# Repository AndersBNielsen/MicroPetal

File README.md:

# MicroPetal Uno R1

[Get the MicroPetal Uno R1 Founders Edition at iMania](https://www.imania.dk/micropetal-uno-r1-founders-edition.htm).

Arduino Uno-format board accommodating PY32F071 and PY32F072. The initial assembly and software target is **PY32F071C1BU6**; F072 software support is not implemented yet.

## Hardware

KiCad sources and fabrication outputs are at the repository root and in `production/`.

## Software

The experimental Arduino core, PlatformIO platform, tools and examples live in [`software/`](software/README.md).

- [Arduino beginner guide](software/docs/ARDUINO-START.md)
- [PlatformIO beginner guide](software/docs/PLATFORMIO-START.md)
- [Schematic analysis and first-power instructions](software/docs/SCHEMATIC-ANALYSIS.md)

Software is compile-tested, not yet hardware-validated.

Run software commands from `software/`, e.g. `cd software` before following either guide.

## Getting a PCB

Prefer a ready-made board? [Get the MicroPetal Uno R1 Founders Edition at iMania](https://www.imania.dk/micropetal-uno-r1-founders-edition.htm). To manufacture your own, use the files in [`production/`](production/).
This project is kindly sponsored by JLCPCB. They offer cheap, professional looking PCBs and super fast delivery.

Step 1: Get the gerber file zip package from the /hardware folder
/hardware/rev2/rev2-1316.zip for instance.

Step 2: Upload to JLCPCB [https://jlcpcb.com](https://jlcpcb.com/?from=Anders_N)

Step 3: Pick your color, surface finish and order.

If you want JLCPCB to assemble a board, the BOM and placement files are also in the repo. 

You can use these affiliate links to get a board for $2 and also get $80 worth of New User Coupons at: https://jlcpcb.com/?from=Anders_N

And in case you also want to order a 3D-printed case you can use this link. 
How to Get a $7 3D Printing Coupon: https://jlc3dp.com/?from=Anders_N

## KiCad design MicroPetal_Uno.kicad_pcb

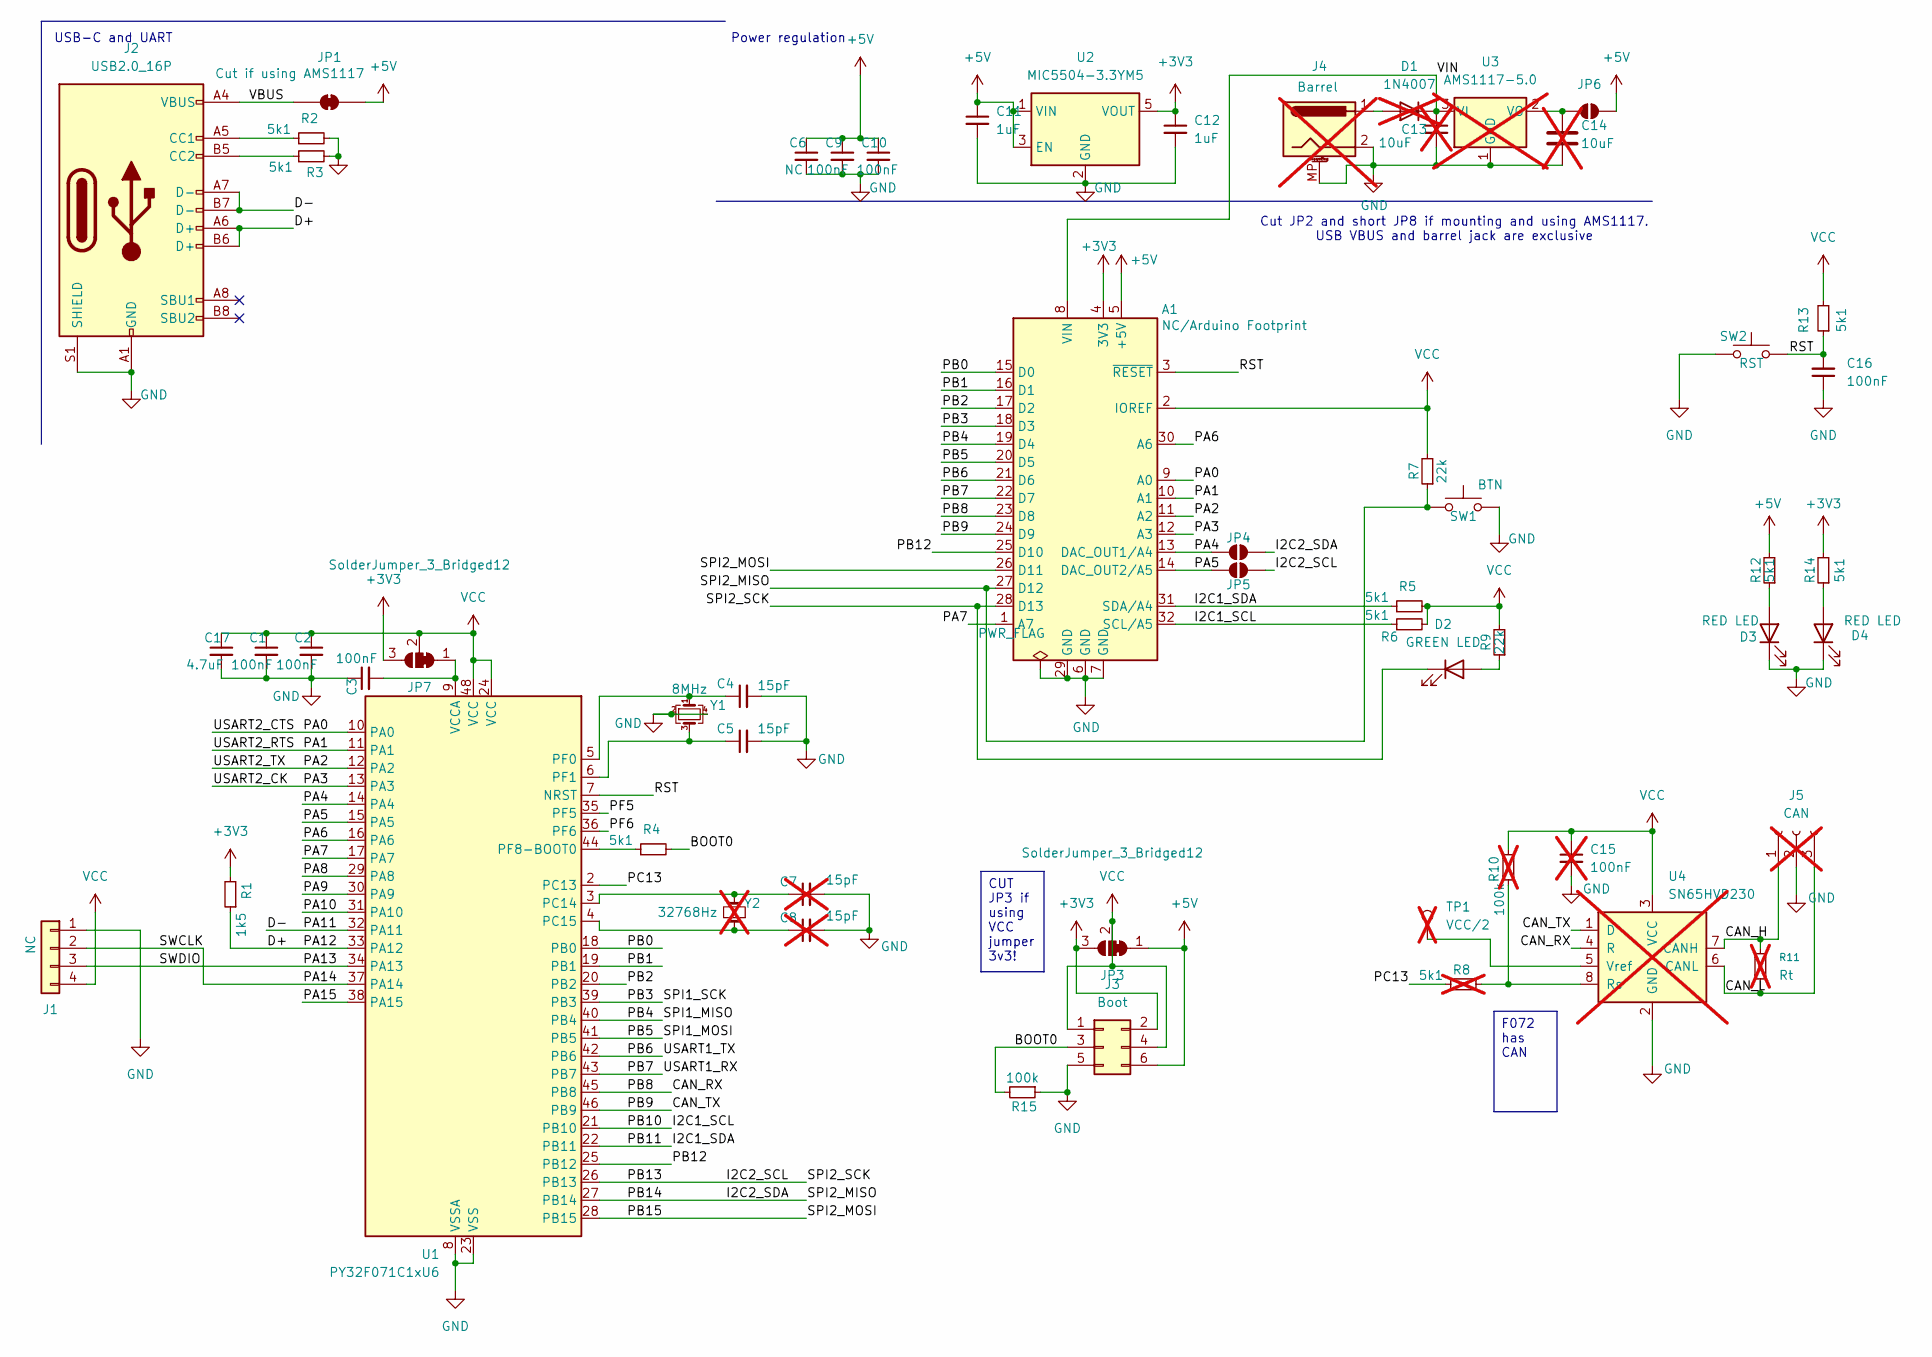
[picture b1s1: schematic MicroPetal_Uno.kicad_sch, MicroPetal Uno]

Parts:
A1: NC/Arduino Footprint; Arduino_UNO_R3_WithMountingHoles
C1, C2, C3, C9, C10, C16: 100nF; C_0402_1005Metric; LCSC C49678
C4, C5: 15pF; C_0402_1005Metric; LCSC C1548
C6: NC; C_0805_2012Metric
C7, C8: 15pF; C_0402_1005Metric; LCSC C1548; not fitted
C11, C12: 1uF; C_0805_2012Metric; LCSC C28323
C13, C14: 10uF; C_1206_3216Metric; LCSC C13585; not fitted
C15: 100nF; C_0402_1005Metric; LCSC C307331; not fitted
C17: 4.7uF; C_0603_1608Metric; LCSC C19666
D1: 1N4007; D_SMA; LCSC C95872; not fitted
D2: GREEN LED; LED_0805_2012Metric; LCSC C2297
D3, D4: RED LED; LED_0805_2012Metric; LCSC C84256
J1: NC; PinHeader_1x04_P2.54mm_Vertical
J2: USB2.0_16P; USB_C_Receptacle_HCTL_HC-TYPE-C-16P-01A; LCSC C2894897
J3: Boot; PinHeader_2x03_P2.54mm_Vertical
J4: Barrel; BarrelJack_Horizontal; not fitted
J5: CAN; PinHeader_1x03_P2.54mm_Vertical; not fitted
JP1: Cut if using AMS1117; SolderJumper-2_P1.3mm_Bridged_RoundedPad1.0x1.5mm
JP3, JP7: SolderJumper_3_Bridged12; SolderJumper-3_P1.3mm_Bridged12_RoundedPad1.0x1.5mm
JP4, JP5, JP6: SolderJumper_2_Open; SolderJumper-2_P1.3mm_Open_RoundedPad1.0x1.5mm
R1: 1k5; R_0402_1005Metric; LCSC C25867
R2, R3, R4, R5, R6, R12, R13, R14: 5k1; R_0402_1005Metric; LCSC C25905
R7, R9: 22k; R_0805_2012Metric; LCSC C17560
R8: 5k1; R_0402_1005Metric; LCSC C25905; not fitted
R10: 100k; R_0402_1005Metric; LCSC C25905; not fitted
R11: Rt; R_0805_2012Metric; not fitted
R15: 100k; R_0402_1005Metric; LCSC C25741
SW1: BTN; SW_SPST_TL3342; LCSC C318884
SW2: RST; SW_SPST_TL3342; LCSC C318884
TP1: VCC/2; TestPoint_Pad_D1.0mm; not fitted
U1: PY32F071C1xU6; QFN-48-1EP_6x6mm_P0.4mm_EP4.4x4.4mm; LCSC C7434410
U2: MIC5504-3.3YM5; SOT-23-5; LCSC C3021093
U3: AMS1117-5.0; SOT-223-3_TabPin2; LCSC C347223; not fitted
U4: SN65HVD230; SOIC-8_3.9x4.9mm_P1.27mm; LCSC C12084; not fitted
Y1: 8MHz; Crystal_SMD_3225-4Pin_3.2x2.5mm; LCSC C5308002
Y2: 32768Hz; Crystal_SMD_3215-2Pin_3.2x1.5mm; LCSC C32346; not fitted

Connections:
+3V3: A1.4 (3V3), C12.1, J3.2, JP3.3 (B), JP7.3 (B), R1.2, R14.2, U2.5 (VOUT)
+5V: A1.5 (+5V), C6.1, C9.1, C10.1, C11.1, J3.6, JP1.2 (B), JP3.1 (A), JP6.2 (B), R12.2, U2.1 (VIN), U2.3 (EN)
/BOOT0: J3.3, R4.2, R15.2
/CAN_H: J5.1, R11.1, U4.7 (CANH)
/CAN_L: J5.3, R11.2, U4.6 (CANL)
/CAN_RX: A1.23 (D8), U1.45 (PB8), U4.4 (R)
/CAN_TX: A1.24 (D9), U1.46 (PB9), U4.1 (D)
/D+: J2.A6 (D+), J2.B6 (D+), R1.1, U1.33 (PA12)
/D-: J2.A7 (D-), J2.B7 (D-), U1.32 (PA11)
/I2C1_SCL: A1.32 (SCL/A5), R6.1, U1.21 (PB10)
/I2C1_SDA: A1.31 (SDA/A4), R5.1, U1.22 (PB11)
/I2C2_SCL: A1.28 (D13), D2.1 (K), JP5.2 (B), U1.26 (PB13)
/I2C2_SDA: A1.27 (D12), JP4.2 (B), R7.1, SW1.1, U1.27 (PB14)
/PA0: A1.9 (A0), U1.10 (PA0)
/PA1: A1.10 (A1), U1.11 (PA1)
/PA2: A1.11 (A2), U1.12 (PA2)
/PA3: A1.12 (A3), U1.13 (PA3)
/PA4: A1.13 (DAC_OUT1/A4), JP4.1 (A), U1.14 (PA4)
/PA5: A1.14 (DAC_OUT2/A5), JP5.1 (A), U1.15 (PA5)
/PA6: A1.30 (A6), U1.16 (PA6)
/PA7: A1.1 (A7), U1.17 (PA7)
/PA8: U1.29 (PA8)
/PA9: U1.30 (PA9)
/PA10: U1.31 (PA10)
/PA13: J1.3, U1.34 (PA13)
/PA14: J1.2, U1.37 (PA14)
/PA15: U1.38 (PA15)
/PB0: A1.15 (D0), U1.18 (PB0)
/PB1: A1.16 (D1), U1.19 (PB1)
/PB2: A1.17 (D2), U1.20 (PB2)
/PB3: A1.18 (D3), U1.39 (PB3)
/PB4: A1.19 (D4), U1.40 (PB4)
/PB5: A1.20 (D5), U1.41 (PB5)
/PB6: A1.21 (D6), U1.42 (PB6)
/PB7: A1.22 (D7), U1.43 (PB7)
/PB12: A1.25 (D10), U1.25 (PB12)
/PB15: A1.26 (D11), U1.28 (PB15)
/PC13: R8.1, U1.2 (PC13)
/PF6: U1.36 (PF6)
/RST: A1.3 (~RESET), C16.2, R13.1, SW2.2, U1.7 (NRST)
/VBUS: J2.A4 (VBUS), J2.A9 (VBUS), J2.B4 (VBUS), J2.B9 (VBUS), JP1.1 (A)
/VIN: A1.8 (VIN), C13.1, D1.1 (K), U3.3 (VI)
unnamed: D1.2 (A), J4.1
unnamed: D2.2 (A), R9.1
unnamed: D3.2 (A), R12.1
unnamed: D4.2 (A), R14.1
unnamed: J2.A5 (CC1), R2.1
unnamed: J2.B5 (CC2), R3.1
unnamed: C14.1, JP6.1 (A), U3.2 (VO)
unnamed: C3.2, JP7.1 (A), U1.9 (VCCA)
unnamed: C7.1, U1.3 (PC14), Y2.2
unnamed: C8.1, U1.4 (PC15), Y2.1
unnamed: C4.1, U1.5 (PF0), Y1.1
unnamed: C5.1, U1.6 (PF1), Y1.3
unnamed: R4.1, U1.44 (PF8-BOOT0)
unnamed: R8.2, R10.1, U4.8 (Rs)
unnamed: TP1.1 (1_1), U4.5 (Vref)
VCC: A1.2 (IOREF), C1.1, C2.1, C15.1, C17.1, J1.4, J3.1, J3.4, JP3.2 (C), JP7.2 (C), R5.2, R6.2, R7.2, R9.2, R10.2, R13.2, U1.24 (VCC), U1.48 (VCC), U4.3 (VCC)

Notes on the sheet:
Cut JP2 and short JP8 if mounting and using AMS1117. USB VBUS and barrel jack are exclusive
Power regulation
USB-C and UART
F072 has CAN
CUT JP3 if using VCC jumper 3v3!

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
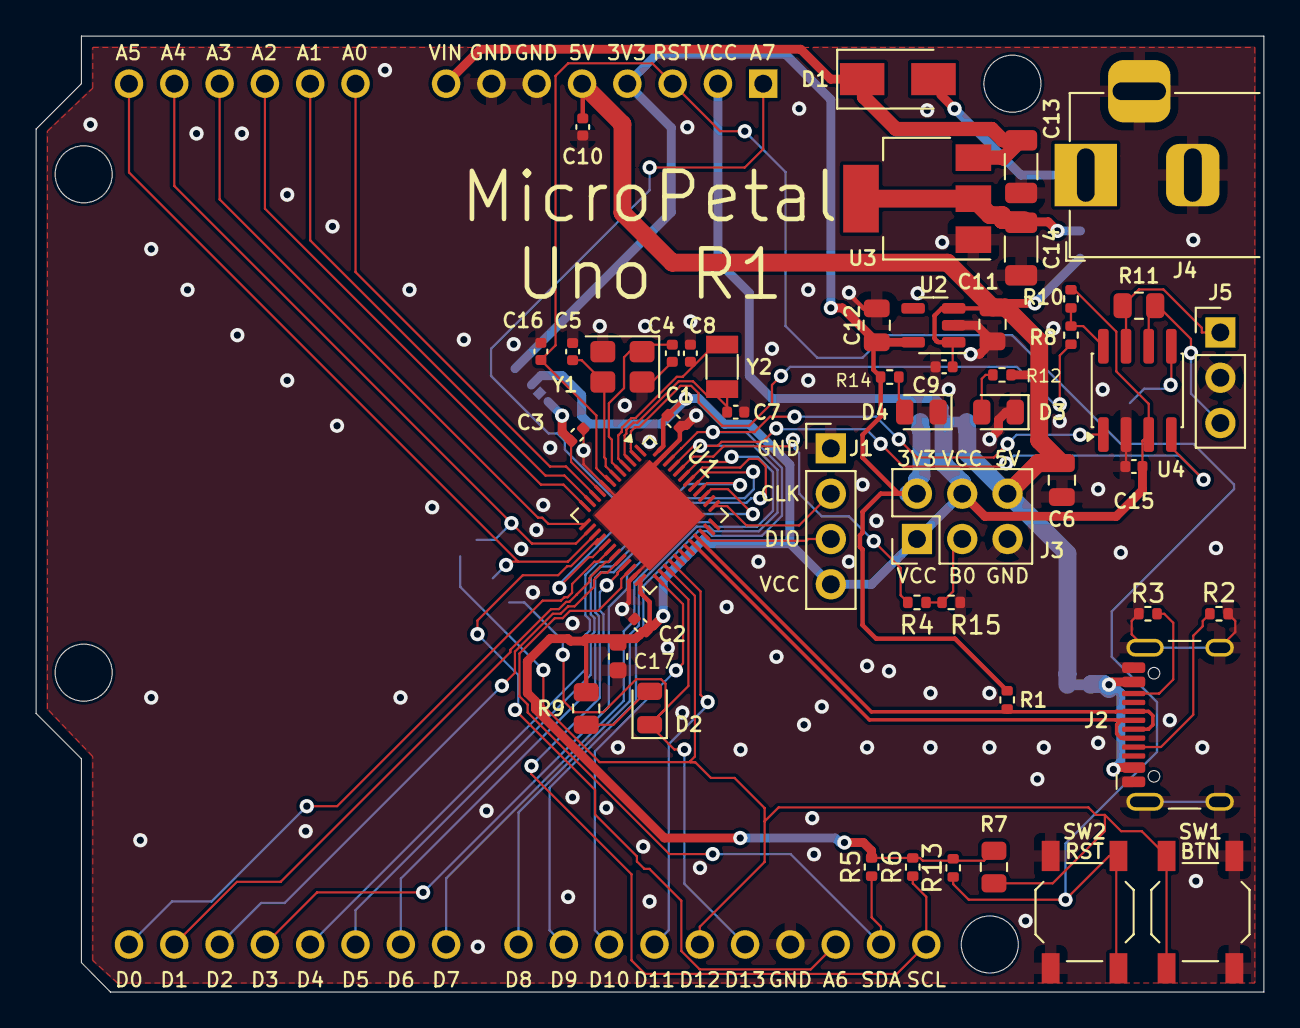
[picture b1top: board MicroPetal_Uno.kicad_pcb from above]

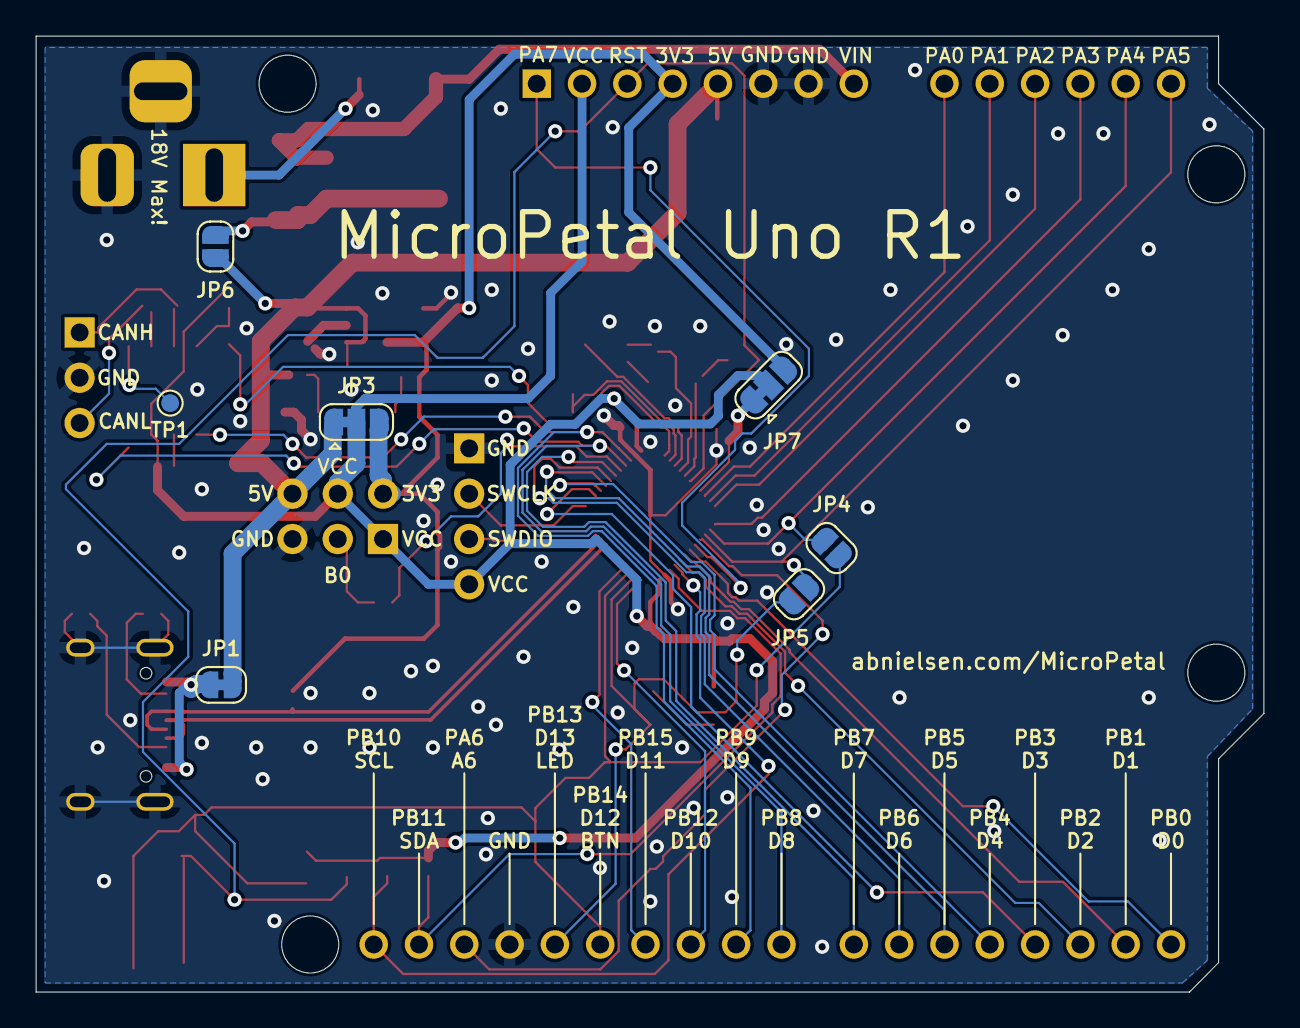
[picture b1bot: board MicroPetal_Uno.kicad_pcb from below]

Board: 2 copper layers, 68.8 x 53.6 mm, 57 parts (8 on the bottom side), 54 nets.

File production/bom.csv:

Designator,Footprint,Quantity,Value,LCSC Part #
A1,Arduino_UNO_R3_WithMountingHoles,1,NC/Arduino Footprint,
"C1, C10, C16, C2, C3, C9",0402,6,100nF,
"C11, C12",0805,2,1uF,C28323
C17,0603,1,4.7uF,
"C4, C5",0402,2,15pF,C1548
C6,0805,1,NC,
D2,0805,1,GREEN LED,C2297
"D3, D4",0805,2,RED LED,C84256
J1,PinHeader_1x04_P2.54mm_Vertical,1,NC,
J2,USB_C_Receptacle_HCTL_HC-TYPE-C-16P-01A,1,USB2.0_16P,C2894897
J3,PinHeader_2x03_P2.54mm_Vertical,1,Boot,
R1,0402,1,1k5,C25867
"R12, R13, R14, R2, R3, R4, R5, R6",0402,8,5k1,
R15,0402,1,100k,
"R7, R9",0805,2,22k,C17560
SW1,SW_SPST_TL3342,1,BTN,C318884
SW2,SW_SPST_TL3342,1,RST,C318884
U1,QFN-48-1EP_6x6mm_P0.4mm_EP4.4x4.4mm,1,PY32F071C1xU6,
U2,SOT-23-5,1,MIC5504-3.3YM5,C3021093
Y1,Crystal_SMD_3225-4Pin_3.2x2.5mm,1,8MHz,C5308002

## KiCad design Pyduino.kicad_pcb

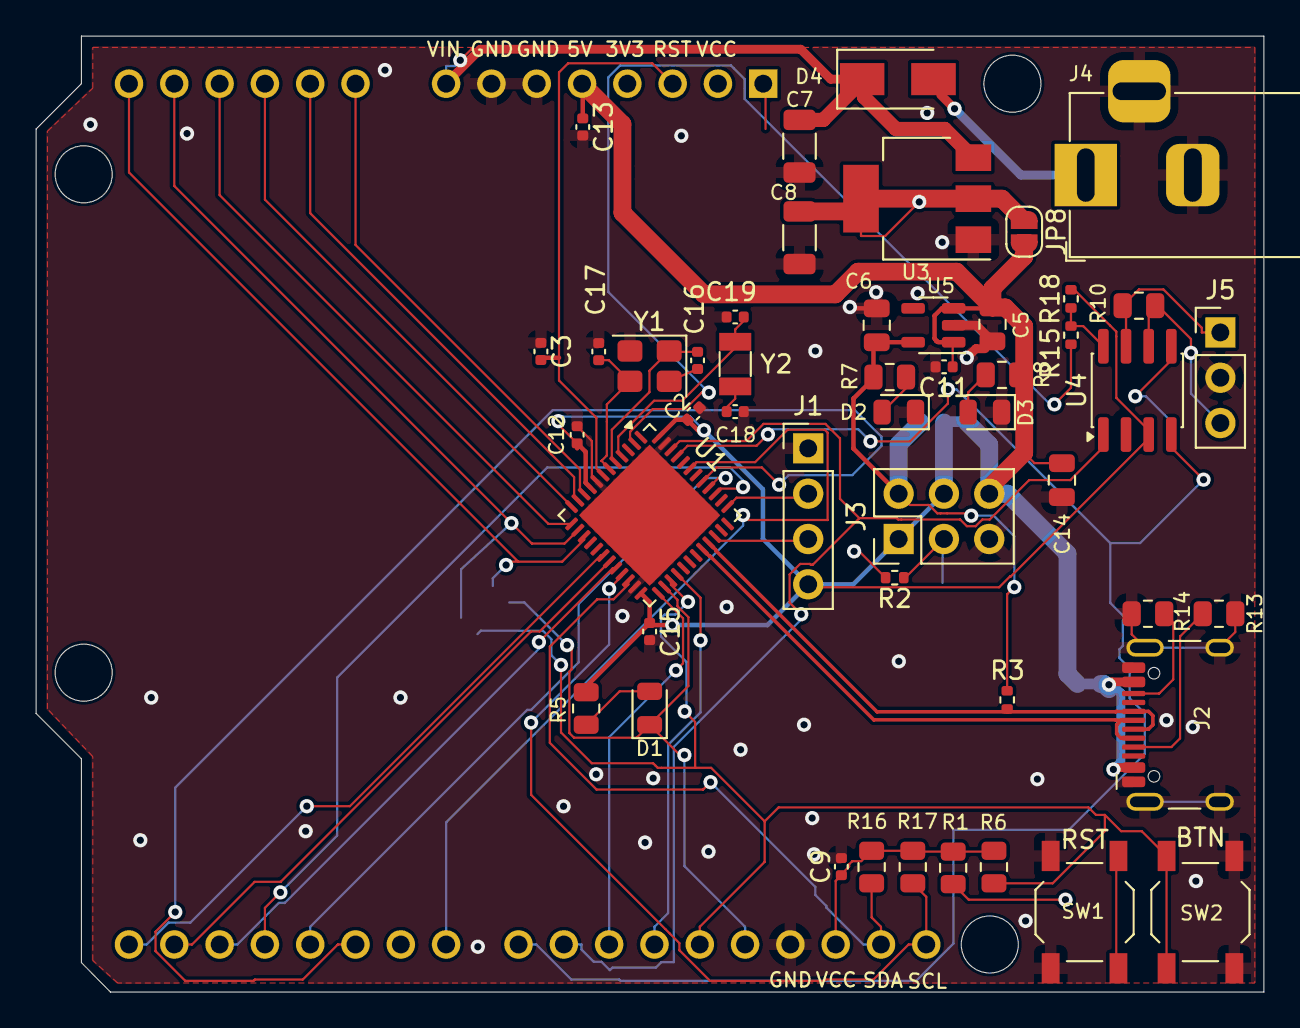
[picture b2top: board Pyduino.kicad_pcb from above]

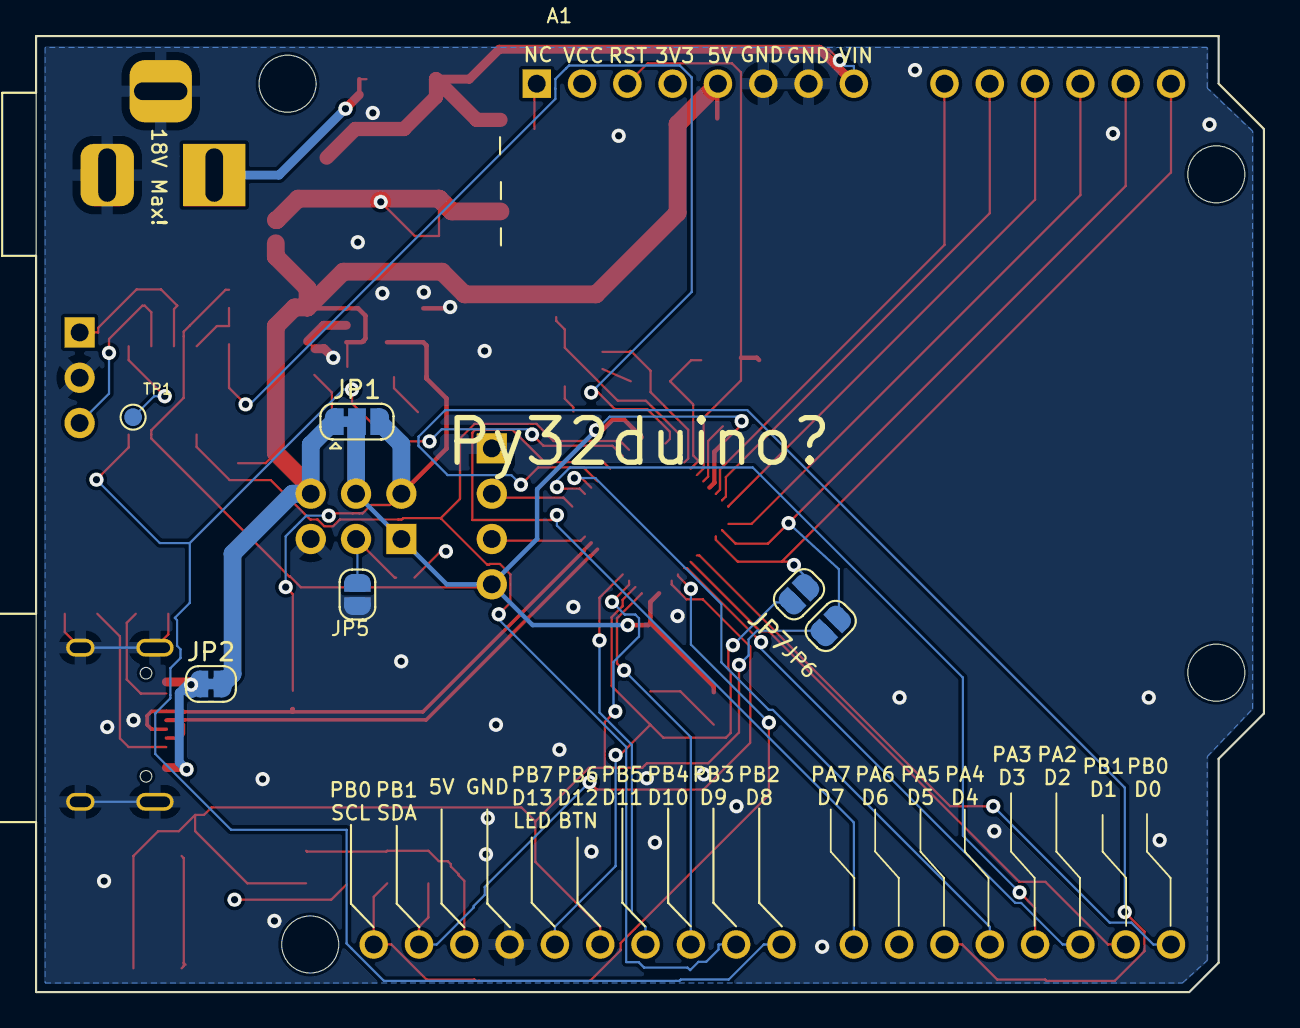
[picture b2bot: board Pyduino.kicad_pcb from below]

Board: 2 copper layers, 68.8 x 53.6 mm, 55 parts (7 on the bottom side), 51 nets.

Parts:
A1: NC/Arduino Footprint; Arduino_UNO_R3_WithMountingHoles
C2, C3, C9, C11, C12, C13, C15: 100nF; C_0402_1005Metric
C5, C6: 1uF; C_0805_2012Metric
C7, C8: 10uF; C_1206_3216Metric
C14: NC; C_0805_2012Metric
C16, C17, C18, C19: 15pF; C_0402_1005Metric
D1: GREEN LED; LED_0805_2012Metric
D2, D3: RED LED; LED_0805_2012Metric
D4: 1N4007; D_SMA
J1: NC; PinHeader_1x04_P2.54mm_Vertical
J2: USB2.0_16P; USB_C_Receptacle_HCTL_HC-TYPE-C-16P-01A
J3: Boot; PinHeader_2x03_P2.54mm_Vertical
J4: Barrel; BarrelJack_Horizontal
J5: CAN; PinHeader_1x03_P2.54mm_Vertical
JP1: SolderJumper_3_Bridged12; SolderJumper-3_P1.3mm_Bridged12_RoundedPad1.0x1.5mm
JP2: Cut if using AMS1117; SolderJumper-2_P1.3mm_Bridged_RoundedPad1.0x1.5mm
JP5, JP6, JP7, JP8: SolderJumper_2_Open; SolderJumper-2_P1.3mm_Open_RoundedPad1.0x1.5mm
R1: 3k; R_0805_2012Metric
R2: 10k; R_0402_1005Metric
R3: 1k5; R_0402_1005Metric
R5, R6, R7, R8: 22k; R_0805_2012Metric
R10: Rt; R_0805_2012Metric
R13, R14, R16, R17: 5k1; R_0805_2012Metric
R15: 5k1; R_0402_1005Metric
R18: 100k; R_0402_1005Metric
SW1: RST; SW_SPST_TL3342
SW2: BTN; SW_SPST_TL3342
TP1: VCC/2; TestPoint_Pad_D1.0mm
U1: PY32F071C1xU6; QFN-48-1EP_7x7mm_P0.5mm_EP5.6x5.6mm
U3: AMS1117-5.0; SOT-223-3_TabPin2
U4: SN65HVD230; SOIC-8_3.9x4.9mm_P1.27mm
U5: MIC5504-3.3YM5; SOT-23-5
Y1: 8MHz; Crystal_SMD_3225-4Pin_3.2x2.5mm
Y2: 32768Hz; Crystal_SMD_3215-2Pin_3.2x1.5mm

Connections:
+3V3: A1.4 (3V3), C6.1, J3.2, JP1.3 (B), R3.2, R7.2, U5.5 (VOUT)
+5V: A1.5 (+5V), C5.1, C11.1, C13.1, C14.1, J3.6, JP1.1 (A), JP2.2 (B), JP8.2 (B), R8.2, U5.1 (VIN), U5.3 (EN)
/BOOT0: J3.3, JP5.1 (A), R2.1
/CAN_H: J5.1, R10.1, U4.7 (CANH)
/CAN_L: J5.3, R10.2, U4.6 (CANL)
/CAN_RX: A1.23 (D8), U1.45 (PB8), U4.4 (R)
/CAN_TX: A1.24 (D9), U1.46 (PB9), U4.1 (D)
/D+: J2.A6 (D+), J2.B6 (D+), R3.1, U1.33 (PA12)
/D-: J2.A7 (D-), J2.B7 (D-), U1.32 (PA11)
/I2C1_SCL: A1.32 (SCL/A5), R17.1, U1.21 (PB10)
/I2C1_SDA: A1.31 (SDA/A4), R16.1, U1.22 (PB11)
/I2C2_SCL: A1.28 (D13), D1.1 (K), JP7.2 (B), U1.26 (PB13)
/I2C2_SDA: A1.27 (D12), JP6.2 (B), R6.1, SW2.1, U1.27 (PB14)
/PA0: A1.9 (A0), U1.10 (PA0)
/PA1: A1.10 (A1), U1.11 (PA1)
/PA2: A1.11 (A2), U1.12 (PA2)
/PA3: A1.12 (A3), U1.13 (PA3)
/PA4: A1.13 (DAC_OUT1/A4), JP6.1 (A), U1.14 (PA4)
/PA5: A1.14 (DAC_OUT2/A5), JP7.1 (A), U1.15 (PA5)
/PA13: J1.3, U1.34 (PA13)
/PA14: J1.2, U1.37 (PA14)
/PB0: A1.15 (D0), U1.18 (PB0)
/PB1: A1.16 (D1), U1.19 (PB1)
/PB2: A1.17 (D2), U1.20 (PB2)
/PB3: A1.18 (D3), U1.39 (PB3)
/PB4: A1.19 (D4), U1.40 (PB4)
/PB5: A1.20 (D5), U1.41 (PB5)
/PB6: A1.21 (D6), U1.42 (PB6)
/PB7: A1.22 (D7), U1.43 (PB7)
/PB12: A1.25 (D10), U1.25 (PB12)
/PB15: A1.26 (D11), U1.28 (PB15)
/PC13: R15.1, U1.2 (PC13)
/RST: A1.3 (~RESET), C3.2, R1.2, SW1.2, U1.7 (NRST)
/VBUS: J2.A4 (VBUS), J2.A9 (VBUS), J2.B4 (VBUS), J2.B9 (VBUS), JP2.1 (A)
/VIN: A1.8 (VIN), C7.1, D4.1 (K), U3.3 (VI)
GND: A1.6 (GND), A1.7 (GND), A1.29 (GND), C2.2, C3.1, C5.2, C6.2, C7.2, C8.2, C9.2, C11.2, C12.2, C13.2, C14.2, C15.2, C16.2, C17.2, C18.2, C19.2, D2.1 (K), D3.1 (K), J1.1, J2.A1 (GND), J2.A12 (GND), J2.B1 (GND), J2.B12 (GND), J2.S1 (SHIELD), J3.5, J4.2, J4.MP (MountPin_MP), J5.2, JP5.2 (B), R13.2, R14.2, SW1.1, SW2.2, U1.8 (VSSA), U1.23 (VSS), U1.47 (VSS), U1.49 (VSS), U3.1 (GND), U4.2 (GND), U5.2 (GND), Y1.2, Y1.4
unnamed: D1.2 (A), R5.1
unnamed: D2.2 (A), R7.1
unnamed: D3.2 (A), R8.1
unnamed: D4.2 (A), J4.1
unnamed: J2.A5 (CC1), R13.1
unnamed: J2.B5 (CC2), R14.1
unnamed: C8.1, JP8.1 (A), U3.2 (VO)
unnamed: C18.1, U1.3 (PC14), Y2.2
unnamed: C19.1, U1.4 (PC15), Y2.1
unnamed: C16.1, U1.5 (PF0), Y1.1
unnamed: C17.1, U1.6 (PF1), Y1.3
unnamed: R2.2, U1.44 (PF8-BOOT0)
unnamed: R15.2, R18.1, U4.8 (Rs)
unnamed: TP1.1 (1_1), U4.5 (Vref)
VCC: A1.2 (IOREF), A1.30 (AREF), C2.1, C9.1, C12.1, C15.1, J1.4, J3.1, J3.4, JP1.2 (C), R1.1, R5.2, R6.2, R16.2, R17.2, R18.2, U1.9 (VCCA), U1.24 (VCC), U1.48 (VCC), U4.3 (VCC)

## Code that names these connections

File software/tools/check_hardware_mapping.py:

#!/usr/bin/env python3
"""Check board table and vector table against analyzed CAD/device sources; no USB access."""
from pathlib import Path
import argparse,re,xml.etree.ElementTree as ET
root=Path(__file__).resolve().parents[1];core=root/'hardware/micropetal/py32/cores/micropetal'
expected=['PB0','PB1','PB2','PB3','PB4','PB5','PB6','PB7','PB8','PB9','PB12','PB15','PB14','PB13']+['PA'+str(i) for i in range(8)]+['PB11','PB10']
actual=['P'+port+bit for port,bit in re.findall(r'\{GPIO([AB]),1<<(\d+)\}',(core/'wiring.cpp').read_text().split('static int')[0])]
assert actual==expected,(actual,expected)
parser=argparse.ArgumentParser(description=__doc__)
parser.add_argument('--netlist',type=Path,help='KiCad XML netlist to check against the core')
args=parser.parse_args()
cad=args.netlist if args.netlist else root/'schematic.net.xml'
if args.netlist and not cad.is_file():parser.error('Netlist does not exist: '+str(cad))
if cad.exists():
 nets=ET.parse(cad).getroot().findall('./nets/net')
 header={str(i):'D'+str(i-15) for i in range(15,29)}
 header.update({'9':'A0','10':'A1','11':'A2','12':'A3','13':'A4','14':'A5','30':'A6','1':'A7','31':'SDA','32':'SCL'})
 names=['D'+str(i) for i in range(14)]+['A'+str(i) for i in range(8)]+['SDA','SCL'];observed={}
 for net in nets:
  labels=[header[n.get('pin')] for n in net if n.get('ref')=='A1' and n.get('pin') in header]
  mcus=[n.get('pinfunction').split('_')[0] for n in net if n.get('ref')=='U1']
  for label in labels:
   assert len(mcus)==1,(label,mcus)
   observed[label]=mcus[0]
 assert [observed[n] for n in names]==expected,observed
irq={int(n):name+'_IRQHandler' for name,n in re.findall(r'(\w+)_IRQn\s*=\s*(\d+)',(core/'device/py32f071xB.h').read_text())}
vector=(core/'startup.S').read_text().split('g_pfnVectors:')[1]
entries=re.findall(r'\.word\s+(\w+)',vector)
assert len(entries)==48
for i in range(32):assert entries[16+i]==irq.get(i,'0'),(i,entries[16+i],irq.get(i))
assert entries[0]=='_estack' and entries[1]=='Reset_Handler'
assert '128K' in (root/'hardware/micropetal/py32/variants/micropetal_uno/linker.ld').read_text()
print('PASS: 24 header pin mappings and 32 F071 peripheral IRQ slots')

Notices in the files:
MicroPetal_Uno.kicad_pcb:
License: https://creativecommons.org/licenses/by-nc/4.0/legalcode
